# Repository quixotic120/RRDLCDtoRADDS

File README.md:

# RRDLCDtoRADDS

Simple conversion board for the RepRapDiscount graphical LCD to work with RADDS

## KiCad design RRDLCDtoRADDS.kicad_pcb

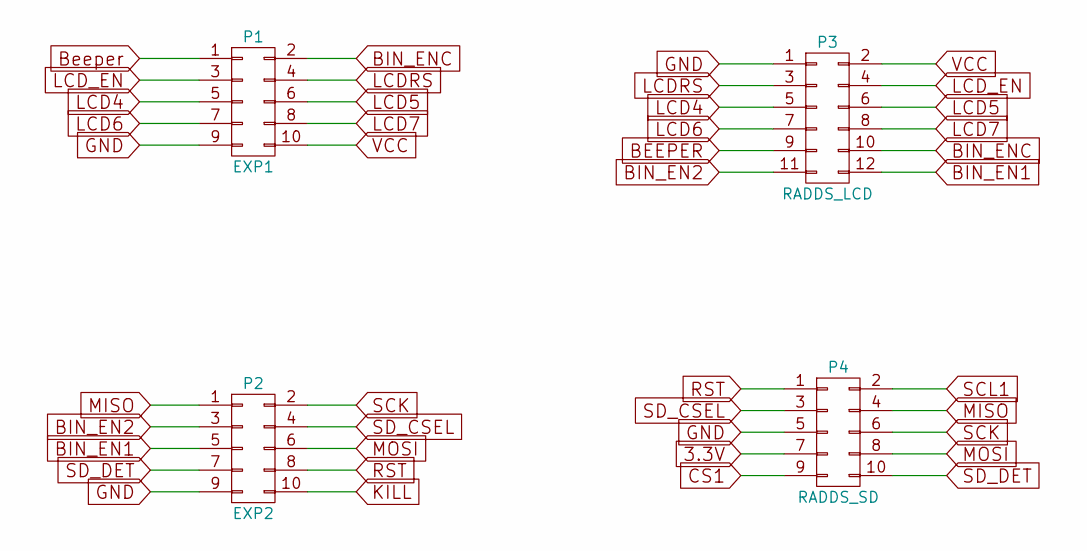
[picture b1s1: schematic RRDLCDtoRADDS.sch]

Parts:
P1: EXP1; Pin_Header_Straight_2x05
P2: EXP2; Pin_Header_Straight_2x05
P3: RADDS_LCD; Pin_Header_Straight_2x06
P4: RADDS_SD; Pin_Header_Straight_2x05

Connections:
3.3V: P4.7
BEEPER: P1.1, P3.9
BIN_EN1: P2.5, P3.12
BIN_EN2: P2.3, P3.11
BIN_ENC: P1.2, P3.10
CS1: P4.9
GND: P1.9, P2.9, P3.1, P4.5
KILL: P2.10
LCD4: P1.5, P3.5
LCD5: P1.6, P3.6
LCD6: P1.7, P3.7
LCD7: P1.8, P3.8
LCDRS: P1.4, P3.3
LCD_EN: P1.3, P3.4
MISO: P2.1, P4.4
MOSI: P2.6, P4.8
RST: P2.8, P4.1
SCK: P2.2, P4.6
SCL1: P4.2
SD_CSEL: P2.4, P4.3
SD_DET: P2.7, P4.10
VCC: P1.10, P3.2

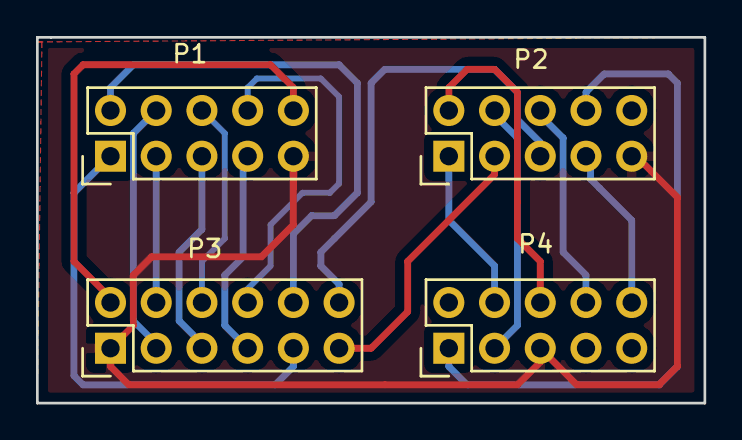
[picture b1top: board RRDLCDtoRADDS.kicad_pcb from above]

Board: 2 copper layers, 37.1 x 20.3 mm, 4 parts (0 on the bottom side), 18 nets.

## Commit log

2016-08-06 init
    RRDtoRadds
